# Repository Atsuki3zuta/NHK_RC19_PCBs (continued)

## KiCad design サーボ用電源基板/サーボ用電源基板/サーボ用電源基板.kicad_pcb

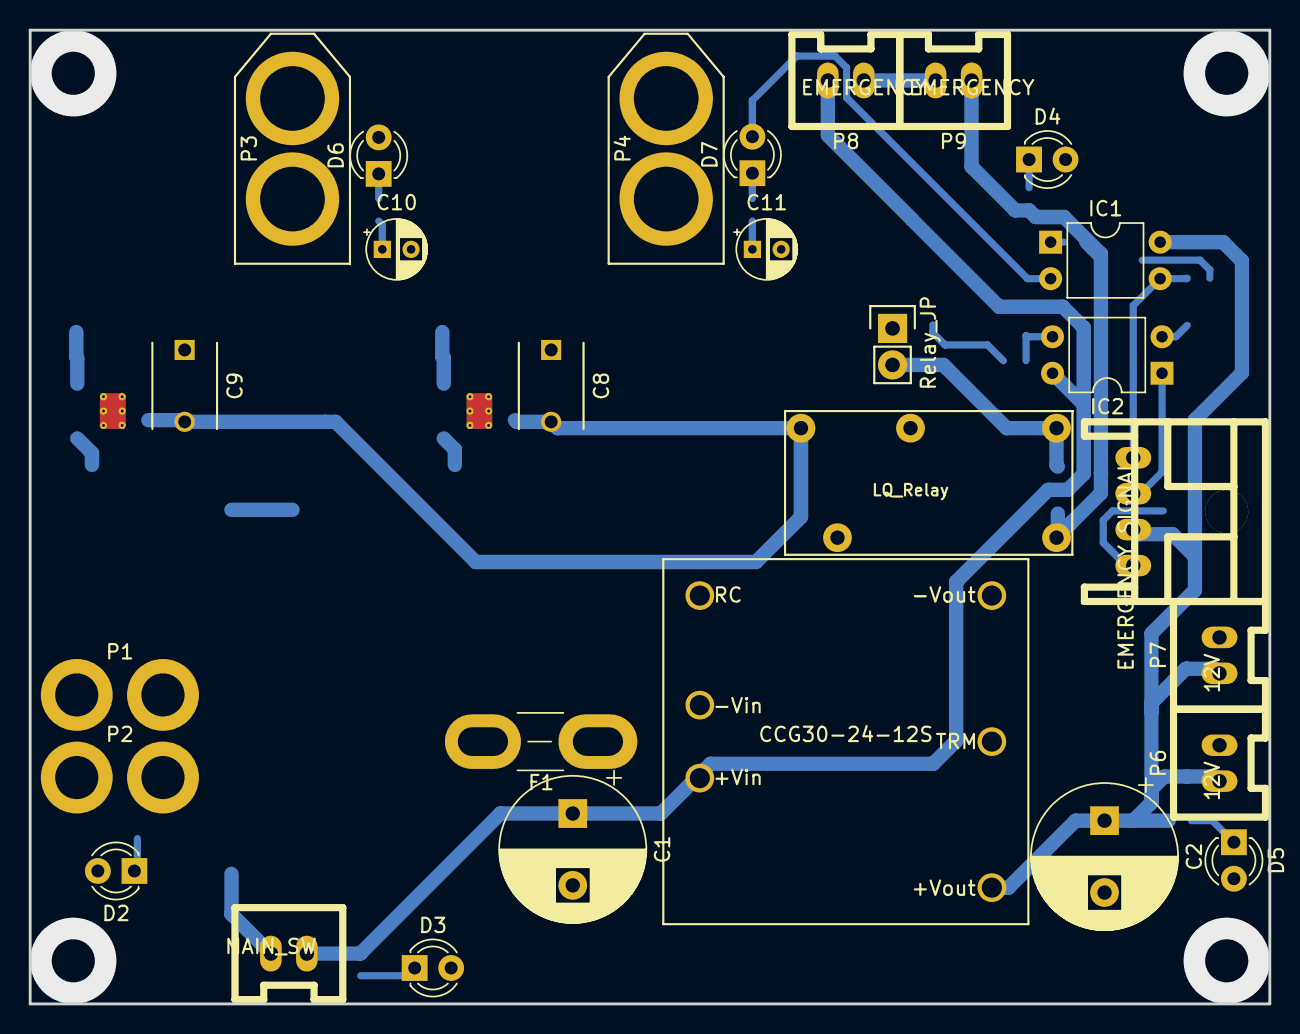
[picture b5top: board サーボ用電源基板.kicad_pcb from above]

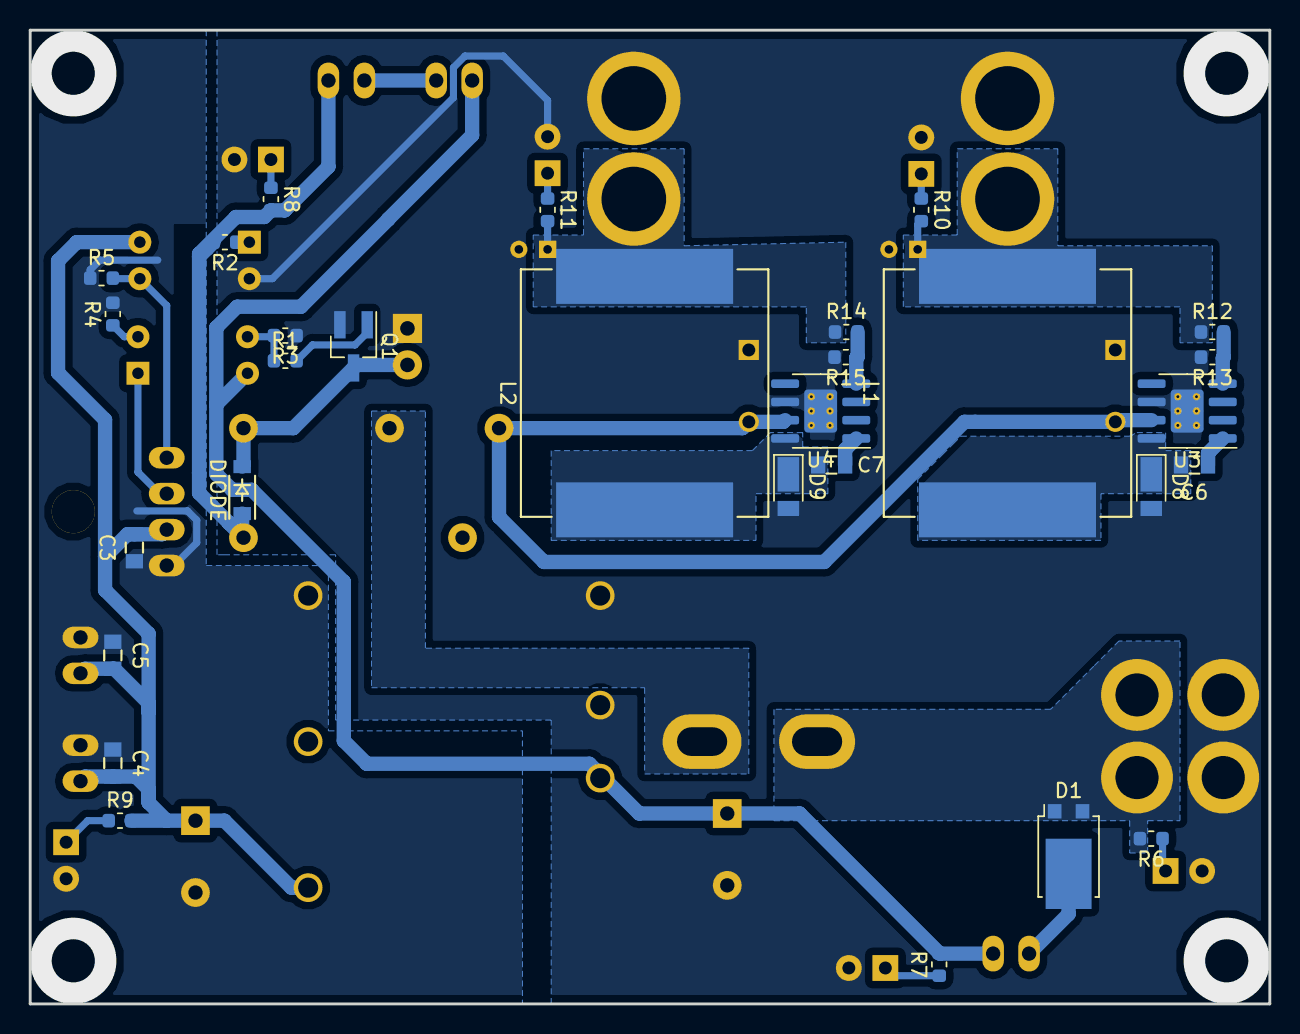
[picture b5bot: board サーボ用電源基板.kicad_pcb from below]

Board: 2 copper layers, 86.2 x 67.8 mm, 57 parts (29 on the bottom side), 31 nets.

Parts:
C1, C2: 470u; CP_Radial_D10.0mm_P5.00mm
C3, C4, C5, C6, C7: 0.1u; C_0603
C8, C9: 10u; C_Disc_D6_P5
C10, C11: 47u; CP_Radial_D4.0mm_P2.00mm
D1: SBR_DIODE; TO-277B
D2: BATT; LED_D3.0mm_Clear
D3: 4Cell_BATT; LED_D3.0mm_Clear
D4: Relay; LED_D3.0mm_Clear
D5: 12V; LED_D3.0mm_Clear
D6: OUT_A; LED_D3.0mm_Clear
D7: OUT_B; LED_D3.0mm_Clear
D8, D9: DIODESCH; D_PowerDI-123
D10: DIODE; SOD-123
F1: FUSE; Fuse_Blade_Mini_directSolder
IC1, IC2: TLP291; DIP-4_W7.62mm
JP1: Relay_JP; Pin_Header_Straight_1x02
L1, L2: 10uH; L_Vishay_IHLP-6767
P1, P2: BATT_IN; PIN2
P3: OUT_A; XT60_T
P4: OUT_B; XT60_T
P5: EMERGENCY_SIGNAL; XA_4LC
P6, P7: 12V; XA_2T
P8, P9: EMERGENCY; XA_2T
P10: MAIN_SW; XA_2T
Q1: MOSFET_N; SOT-23_Handsoldering
R1: 10; R_0603_1608Metric
R2, R6, R7, R8, R9, R13, R15: 2.2k; R_0603_1608Metric
R3, R5, R12, R14: 10k; R_0603_1608Metric
R4: 330; R_0603_1608Metric
R10, R11: 1k; R_0603_1608Metric
U1: CCG30-24-12S; CCG30-24-xxS
U2: LQ_Relay
U3, U4: RT8289; SOIC-8-1EP_3.9x4.9mm_P1.27mm_EP2.29x3mm_ThermalVias

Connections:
4Cell_BATT: C1.1, IC2.4, P8.1, P10.1, R7.2, U1.3
7V_OUTA: C10.1, L1.2, P3.2, R10.2, R12.1
7V_OUTB: C11.1, L2.2, P4.2, R11.2, R14.1
+12V: C2.1, C3.2, C4.2, C5.2, IC1.4, P5.2, P6.2, P7.2, R9.2, U1.6
+BATT: D1.1, D1.2, F1.2, P1.2, P2.2, R6.2
/FB_A: R12.2, R13.1, U3.4
/FB_B: R14.2, R15.1, U4.4
/Force_Shutdown: IC2.1, P5.3
/Relay_State: IC1.3, P5.4, R5.2
DCDC_BATT: C8.2, C9.2, U2.4, U3.7, U4.7
GND: C2.2, C3.1, C4.1, C5.1, D5.2, P5.1, P6.1, P7.1, R4.2, R5.1, U1.4
GNDPWR: C1.2, C8.1, C9.1, C10.2, C11.2, D2.2, D3.2, D4.2, D6.2, D7.2, D8.2, D9.2, IC1.2, JP1.1, P1.1, P2.1, P3.1, P4.1, Q1.2, R3.1, R13.2, R15.2, U1.1, U1.2, U3.6, U3.9, U4.6, U4.9
unnamed: C6.1, U3.1
unnamed: C6.2, D8.1, L1.1, U3.8
unnamed: C7.1, U4.1
unnamed: C7.2, D9.1, L2.1, U4.8
unnamed: D1.3, P10.2
unnamed: D2.1, R6.1
unnamed: D3.1, R7.1
unnamed: D4.1, R8.1
unnamed: D5.1, R9.1
unnamed: D6.1, R10.1
unnamed: D7.1, R11.1
unnamed: F1.1, U2.3
unnamed: IC1.1, R2.1
unnamed: IC2.2, R4.1
unnamed: IC2.3, R1.1, R3.2
unnamed: P8.2, P9.1
unnamed: Q1.1, R1.2
Relay_BATT: D10.1, P9.2, R2.2, R8.2, U2.1
Relay_OUT: D10.2, JP1.2, Q1.3, U2.2

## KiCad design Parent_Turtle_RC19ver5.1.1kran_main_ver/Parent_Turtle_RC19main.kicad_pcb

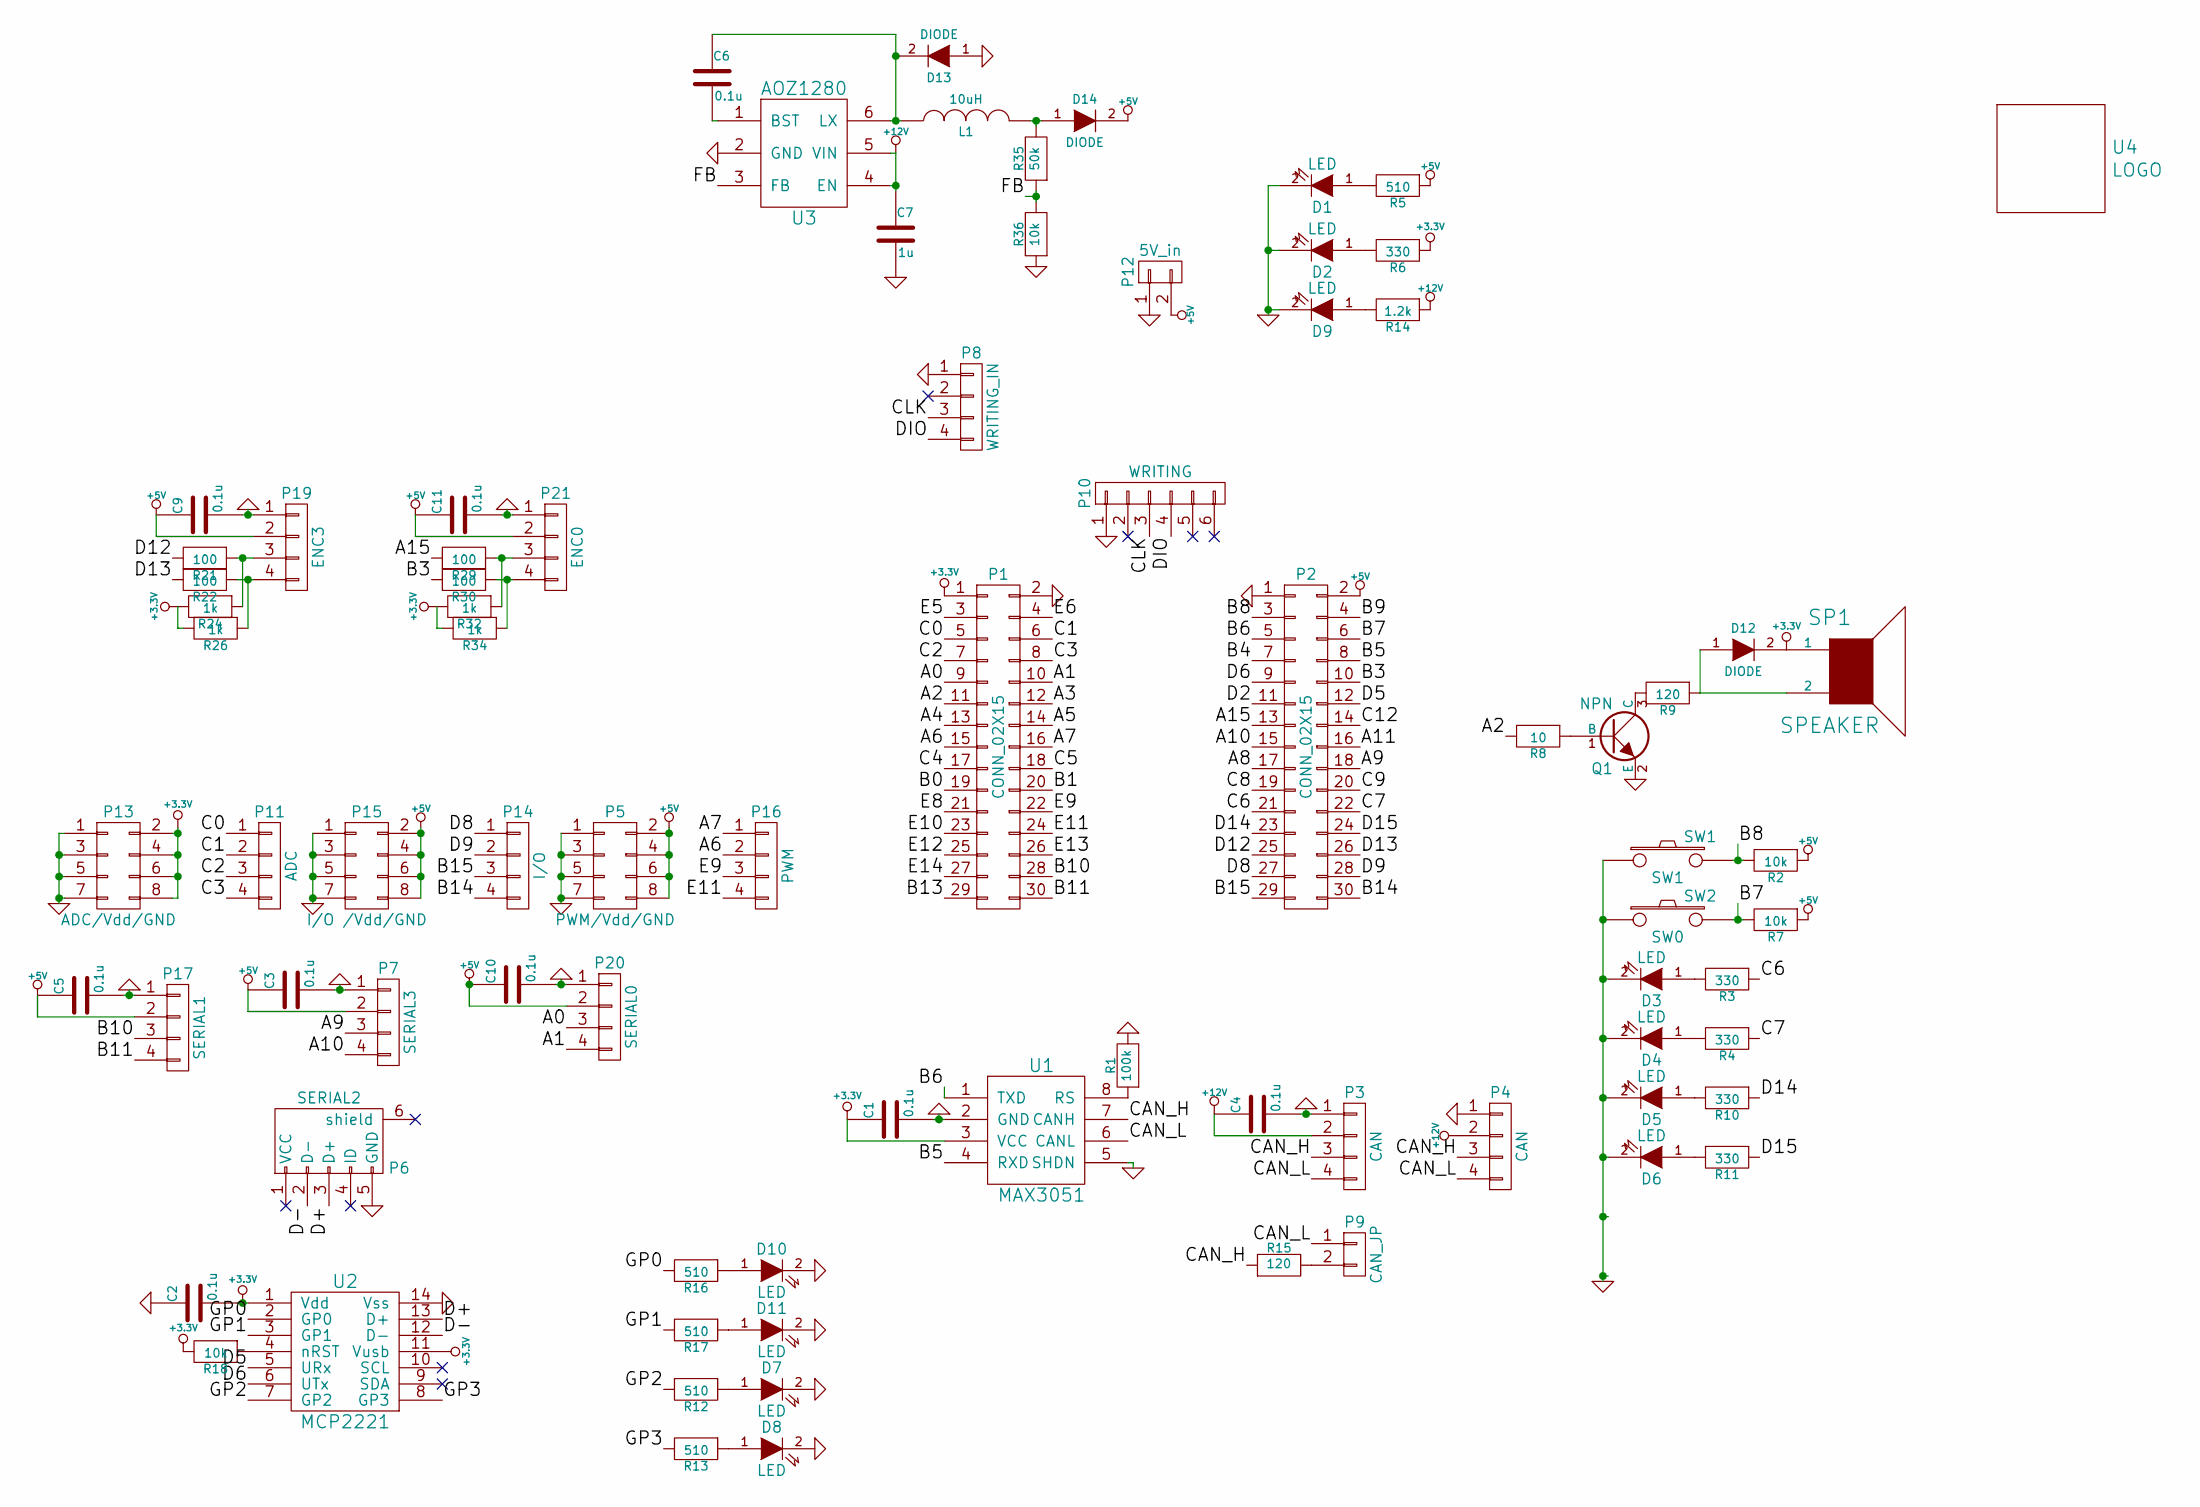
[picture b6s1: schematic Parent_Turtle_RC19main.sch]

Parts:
C1, C2, C3, C4, C5, C6, C9, C10, C11: 0.1u; C_0603
C7: 1u; C_0603
D1, D2, D3, D4, D5, D6, D9: LED; LED-3MM
D7, D8, D10, D11: LED; LED_0603
D12, D13, D14: DIODE; SOD-123
L1: 10uH; Inductor_Taiyo-Yuden_NR-50xx_HandSoldering
P1, P2: CONN_02X15; Socket_Strip_Straight_2x15
P3: CAN; XA_4T
P4: CAN; XA_4LC
P5: PWM/Vdd/GND; PinHeader_2x04_P2.54mm_Vertical
P6: SERIAL2; USB_Mini-B
P7: SERIAL3; XA_4T
P8: WRITING_IN; XA_4LC
P9: CAN_JP; Pin_Header_Straight_1x02
P10: WRITING; Socket_Strip_Straight_1x06
P11: ADC; Pin_Header_Straight_1x04
P12: 5V_in; XA_2T
P13: ADC/Vdd/GND; Pin_Header_Straight_2x04
P14: I/O; Pin_Header_Straight_1x04
P15: I/O /Vdd/GND; Pin_Header_Straight_2x04
P16: PWM; PinHeader_1x04_P2.54mm_Vertical
P17: SERIAL1; XA_4T
P19: ENC3; XA_4T
P20: SERIAL0; XA_4T
P21: ENC0; XA_4T
Q1: NPN; SOT-23
R1: 100k; R_0603
R2, R7, R18, R36: 10k; R_0603
R3, R4, R6, R10, R11: 330; R_0603
R5, R12, R13, R16, R17: 510; R_0603
R8: 10; R_0603
R9, R15: 120; R_0603
R14: 1.2k; R_0603
R21, R22, R29, R30: 100; R_0603
R24, R26, R32, R34: 1k; R_0603
R35: 50k; R_0603
SP1: SPEAKER; UGCT7525AN4
SW1: SW1; RP_TroughHole_Button
SW2: SW0; RP_TroughHole_Button
U1: MAX3051; SOIC-8_3.9x4.9mm_Pitch1.27mm
U2: MCP2221; SOIC-14_3.9x8.7mm_Pitch1.27mm
U3: AOZ1280; TSOT-6-MK06A
U4: LOGO; Turtle_Logo_15.0x15.0

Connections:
+3.3V: C1.1, C2.2, D12.2 (K), P1.1, P13.2, P13.4, P13.6, P13.8, R6.1, R18.2, R24.2, R26.2, R32.2, R34.2, SP1.1, U1.3 (VCC), U2.1 (Vdd), U2.11 (Vusb)
+5V: C3.1, C5.1, C9.1, C10.1, C11.1, D14.2 (K), P2.2, P5.2, P5.4, P5.6, P5.8, P7.2, P12.2, P15.2, P15.4, P15.6, P15.8, P17.2, P19.2, P20.2, P21.2, R2.1, R5.1, R7.1
+12V: C4.1, C7.1, P3.2, P4.2, R14.1, U3.4 (EN), U3.5 (VIN)
/A0: P1.9, P20.3
/A1: P1.10, P20.4
/A2: P1.11, R8.2
/A3: P1.12
/A4: P1.13
/A5: P1.14
/A6: P1.15, P16.2
/A7: P1.16, P16.1
/A8: P2.17
/A9: P2.18, P7.3
/A10: P2.15, P7.4
/A11: P2.16
/A15: P2.13, R29.2
/B0: P1.19
/B1: P1.20
/B3: P2.10, R30.2
/B4: P2.7
/B5: P2.8, U1.4 (RXD)
/B6: P2.5, U1.1 (TXD)
/B7: P2.6, R7.2, SW2.2
/B8: P2.3, R2.2, SW1.2
/B9: P2.4
/B10: P1.28, P17.3
/B11: P1.30, P17.4
/B13: P1.29
/B14: P2.30, P14.4
/B15: P2.29, P14.3
/C0: P1.5, P11.1
/C1: P1.6, P11.2
/C2: P1.7, P11.3
/C3: P1.8, P11.4
/C4: P1.17
/C5: P1.18
/C6: P2.21, R3.1
/C7: P2.22, R4.1
/C8: P2.19
/C9: P2.20
/C12: P2.14
/CAN_H: P3.3, P4.3, R15.1, U1.7 (CANH)
/CAN_L: P3.4, P4.4, P9.1, U1.6 (CANL)
/CLK: P8.3, P10.3
/D2: P2.11
/D5: P2.12, U2.5 (URx)
/D6: P2.9, U2.6 (UTx)
/D8: P2.27, P14.1
/D9: P2.28, P14.2
/D12: P2.25, R21.2
/D13: P2.26, R22.2
/D14: P2.23, R10.1
/D15: P2.24, R11.1
/D+: P6.3 (D+), U2.13 (D+)
/D-: P6.2 (D-), U2.12 (D-)
/DIO: P8.4, P10.4
/E5: P1.3
/E6: P1.4
/E8: P1.21
/E9: P1.22, P16.3
/E10: P1.23
/E11: P1.24, P16.4
/E12: P1.25
/E13: P1.26
/E14: P1.27
/FB: R35.1, R36.2, U3.3 (FB)
/GP0: R16.2, U2.2 (GP0)
/GP1: R17.2, U2.3 (GP1)
/GP2: R12.2, U2.7 (GP2)
/GP3: R13.2, U2.8 (GP3)
GND: C1.2, C2.1, C3.2, C4.2, C5.2, C7.2, C9.2, C10.2, C11.2, D1.2 (K), D2.2 (K), D3.2 (K), D4.2 (K), D5.2 (K), D6.2 (K), D7.2 (K), D8.2 (K), D9.2 (K), D10.2 (K), D11.2 (K), D13.1 (A), P1.2, P2.1, P3.1, P4.1, P5.1, P5.3, P5.5, P5.7, P6.5 (GND), P7.1, P8.1, P10.1, P12.1, P13.1, P13.3, P13.5, P13.7, P15.1, P15.3, P15.5, P15.7, P17.1, P19.1, P20.1, P21.1, Q1.2 (E), R1.2, R36.1, SW1.1, SW2.1, U1.2 (GND), U1.5 (SHDN), U2.14 (Vss), U3.2 (GND)
unnamed: C6.1, D13.2 (K), L1.1, U3.6 (LX)
unnamed: C6.2, U3.1 (BST)
unnamed: D1.1 (A), R5.2
unnamed: D2.1 (A), R6.2
unnamed: D3.1 (A), R3.2
unnamed: D4.1 (A), R4.2
unnamed: D5.1 (A), R10.2
unnamed: D6.1 (A), R11.2
unnamed: D7.1 (A), R12.1
unnamed: D8.1 (A), R13.1
unnamed: D9.1 (A), R14.2
unnamed: D10.1 (A), R16.1
unnamed: D11.1 (A), R17.1
unnamed: D12.1 (A), R9.1, SP1.2
unnamed: D14.1 (A), L1.2, R35.2
unnamed: P9.2, R15.2
unnamed: P19.3, R21.1, R24.1
unnamed: P19.4, R22.1, R26.1
unnamed: P21.3, R29.1, R32.1
unnamed: P21.4, R30.1, R34.1
unnamed: Q1.1 (B), R8.1
unnamed: Q1.3 (C), R9.2
unnamed: R1.1, U1.8 (RS)
unnamed: R18.1, U2.4 (nRST)

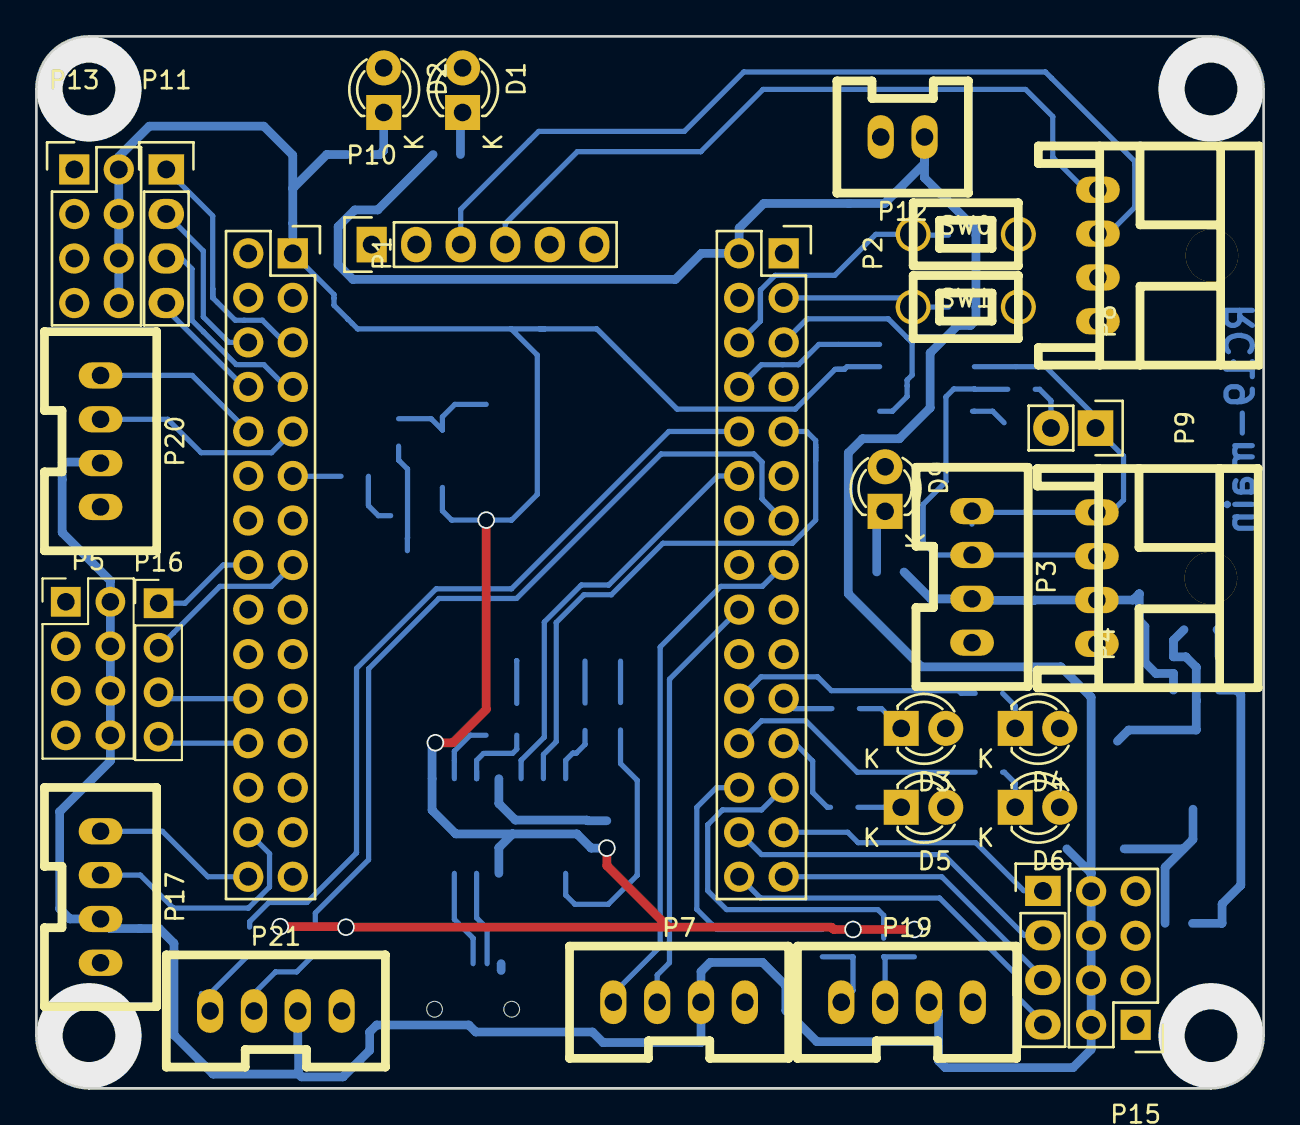
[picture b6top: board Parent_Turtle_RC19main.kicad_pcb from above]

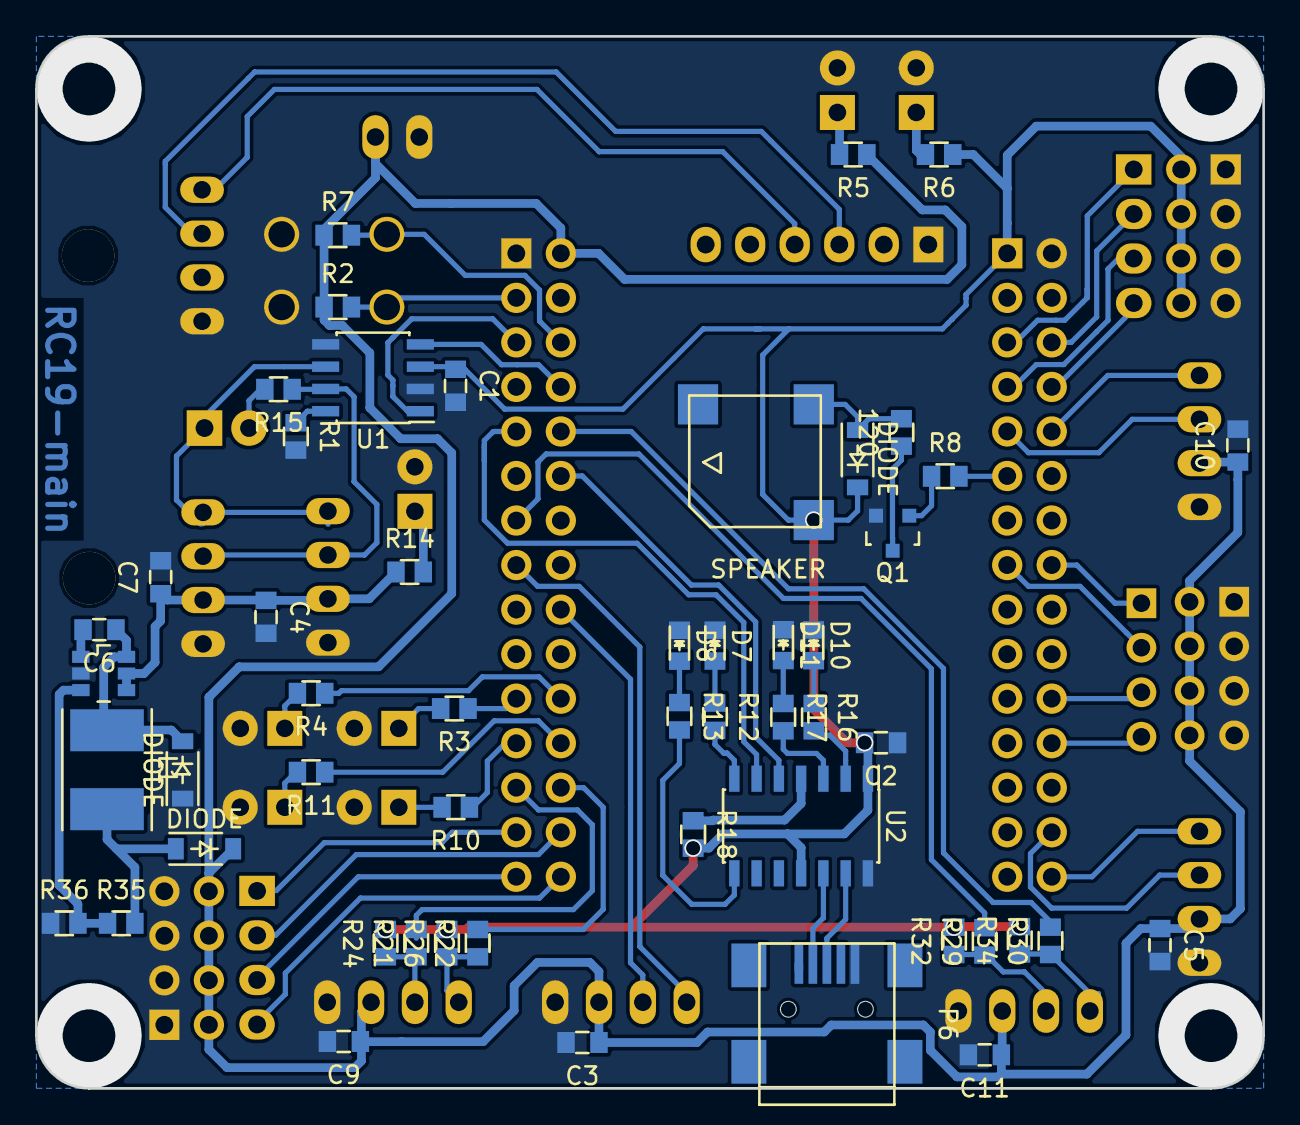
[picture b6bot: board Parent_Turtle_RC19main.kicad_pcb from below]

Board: 2 copper layers, 70.0 x 60.0 mm, 80 parts (52 on the bottom side), 72 nets.

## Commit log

2018-10-15 Add main circuit for No1 video.
2018-10-15 Add circuit graph.
2018-10-17 complete servo main ver.1.0
2018-10-24 A/Dコンバータのピンの追加
2018-10-25 バージョンを上げた
2018-11-20 ver.3(USB→USART CONVERTER)プロジェクトを上げた．
2018-11-20 PWM出力できるピンを増やした．
2018-11-27 多分最終版
2018-12-17 Increase pwm-pins
2018-12-18 シリアル2まで追加
2018-12-19 シリアルの番号の整理
2018-12-21 main基板最終版
2018-12-22 加工データを追加した．
2018-12-25 Add Parent Turtle ver.4, ver.5
2019-01-08 クランリンケージ用main基板完成版
2019-01-08 ver.5は本当にこれが完成版.
2019-01-08 ポート表いじった.
2019-01-22 色々修正と回路図を追加、電源基板を改良した.
2019-01-26 インダクタのフットプリントの修正.
2019-01-31 神子島君リンクmain基板は完成.
2019-01-31 complete project klan linkage main.
2019-02-07 kagoshima link main.
2019-02-07 RC19 main 途中.
2019-02-08 良い感じ.
2019-02-08 あと四本.
2019-02-09 完成版.
2019-02-12 cosmos -> Centaurus, 加工データの追加.
2019-02-12 一旦挙げておく.
2019-02-12 kagoshima_link_main.
2019-02-12 完成（仮）
2019-02-26 実験用電源基板(うちで加工する用)
2019-02-26 Add MR2 main circuit project.
2019-02-26 一応完成.
2019-03-11 MR2-main修正版. 電源周りの修正が必要,要小型化.
2019-03-11 Lipo-Alarm 一応完成版.
2019-03-11 ver.0とver.1の両方をあげておく.
2019-03-14 RC19 mains.
2019-03-18 main 完成
2019-03-18 完成,製造ファイル生成
2019-03-30 あ～、ミスを見つけてしまったよ．なえる．
2019-03-30 とちゅう
2019-04-09 とりあえず、問題なければ完了.
2019-04-09 電源配線完了.フルカラーの秋月のエンコーダ基板面積的に使用できなかった...
2019-04-09 一応、問題なさげ.
2019-04-09 これはくそ基板.
2019-04-13 フォトインタラプタ、隙間大きい完成
2019-04-13 KlanLinkage ver.1.0
2019-04-13 電源電圧電流監視電源基板
2019-04-13 これで終わりであって欲しい.
2019-04-13 エンコーダ:-2,シリアル+1,PWM+4,元クラン、Newパク
2019-04-13 mainの加工データ
2019-04-13 配線完了.
2019-04-15 加工データを追加しただけ
2019-04-15 既存の電源基板を6Cell専用にした感はある.
2019-04-15 パク君のシールドmain基板.
2019-04-15 リポアラーム,XHにして抜けにくくした奴,途中
2019-04-15 パク上がっていなかったやつ
2019-04-15 電源、上がっていなかったやつ
2019-04-16 mainは加工データを追加,電源はビアホールなどの配線の改良.
2019-04-22 ブザとRC-LPFの抵抗が干渉してしまっていたため、配置を変えた
2019-04-22 No meaning
2019-04-22 ステンシル自作実験台ファイルを生成した
2019-04-25 可変電圧I/Oのところにシルクを追加,製造ファイル追加
2019-04-25 No meaning.
2019-04-26 no message.
2019-05-02 恐らくエネルギー破壊で燃えた
2019-05-02 ピカチュウひとまず完成.
2019-05-02 緑ピカチュウか何か
2019-05-03 ピカチュウたちの配線を変えた。
2019-05-03 Red Bull.
2019-05-04 回路図,基板図を作成した.
2019-05-04 資料のコス用の基板外形サイズなどの出力.
2019-05-04 ピカチュウ.
2019-05-09 Back UP.
2020-02-26 そういえば，RC19の基板整理していなかった(リポジトリ的にも)
